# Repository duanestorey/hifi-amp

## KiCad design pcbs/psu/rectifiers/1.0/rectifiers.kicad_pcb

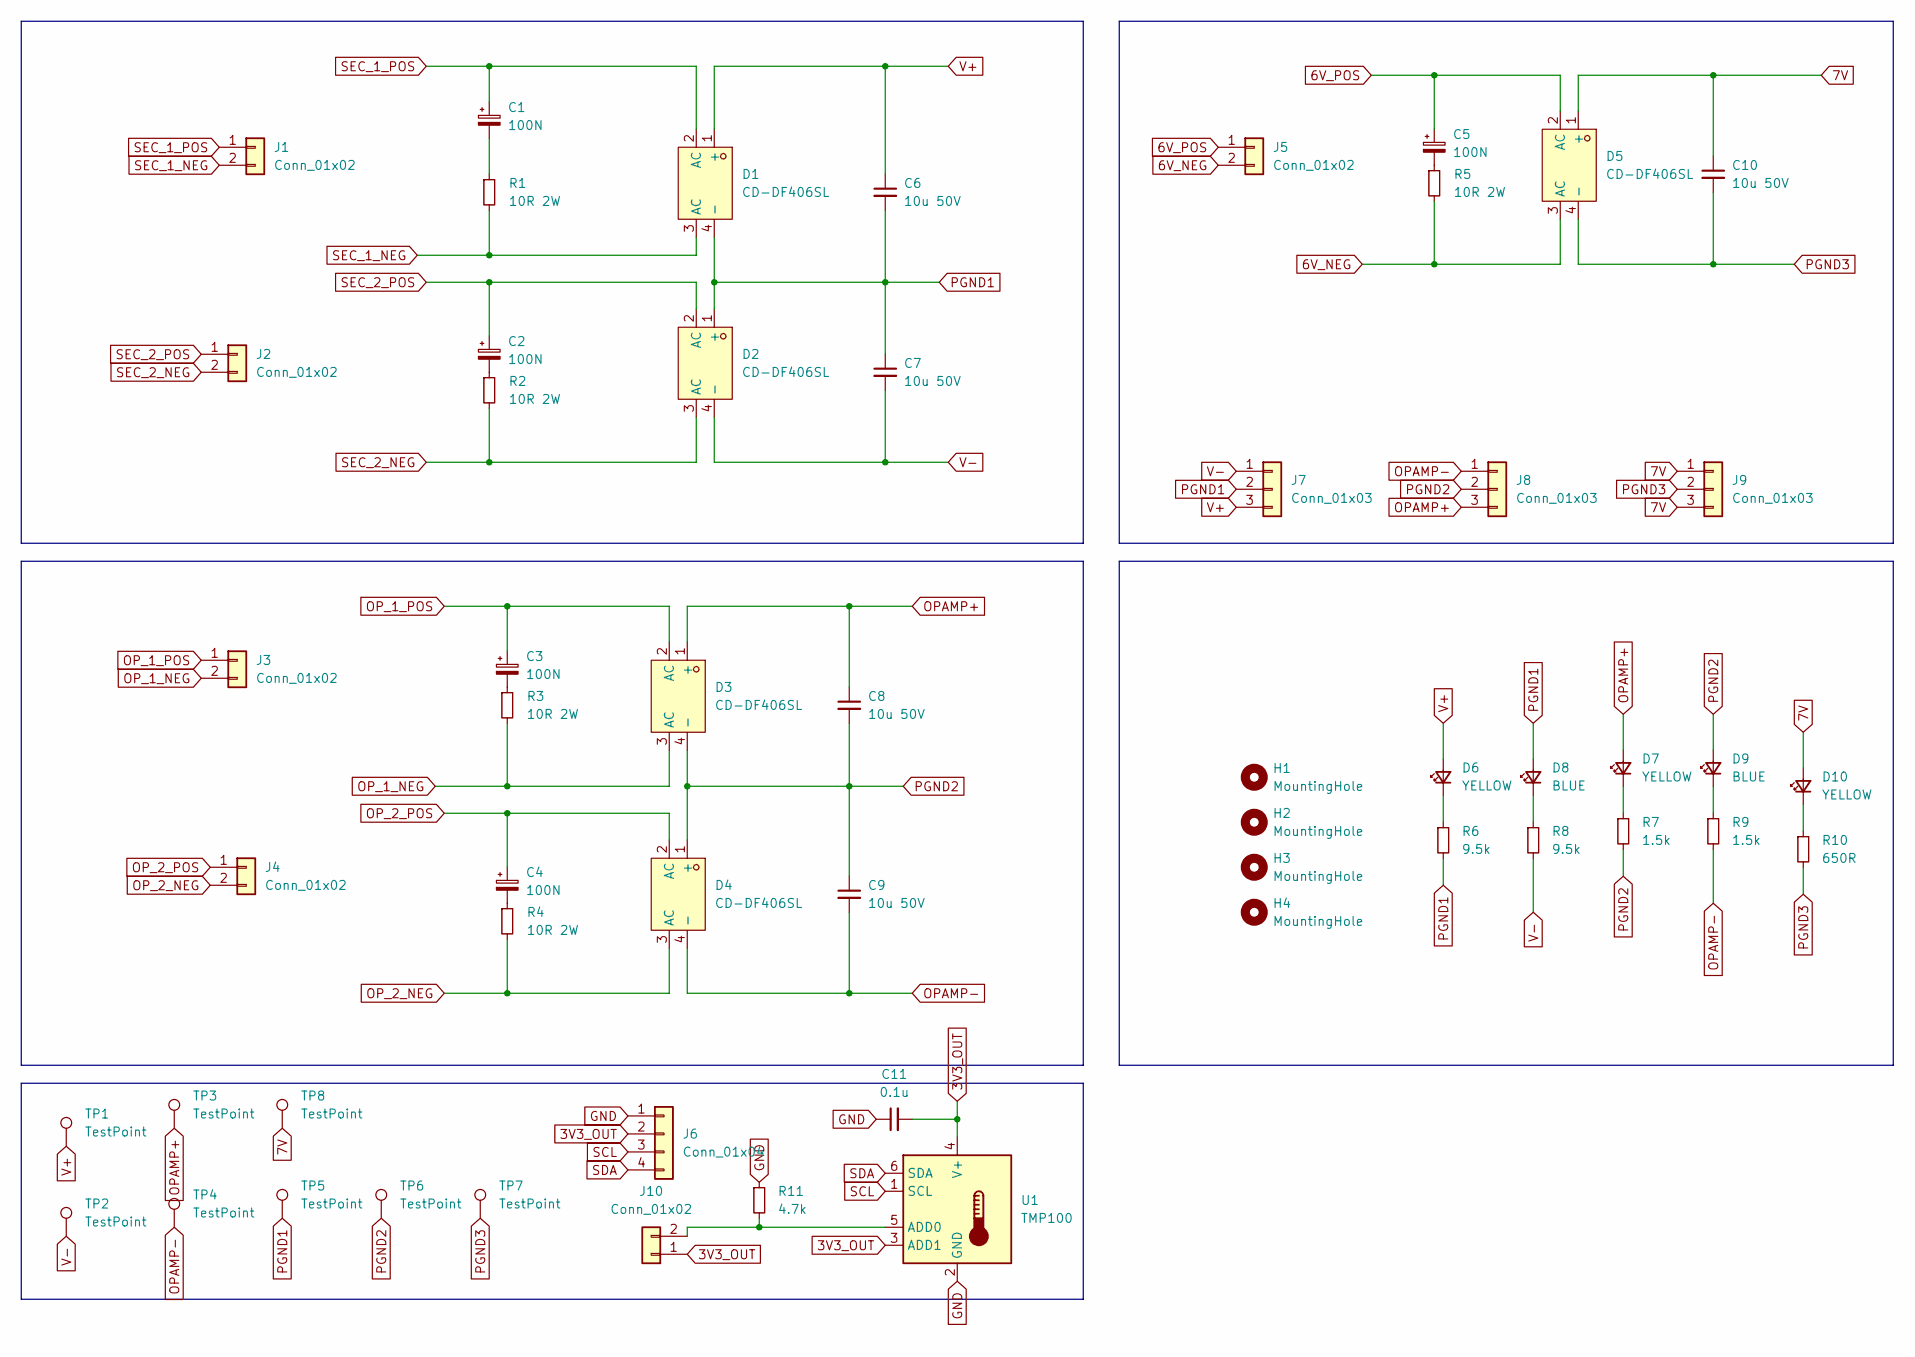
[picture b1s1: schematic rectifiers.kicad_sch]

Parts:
C1, C2, C3, C4, C5: 100N; C_Rect_L10.3mm_W4.5mm_P7.50mm_MKS4; Mouser MKP4F031002D00KF00
C6, C7, C8, C9, C10: 10u 50V; C_1206_3216Metric_Pad1.33x1.80mm_HandSolder
C11: 0.1u; C_0805_2012Metric_Pad1.18x1.45mm_HandSolder
D1, D2, D3, D4, D5: CD-DF406SL; Z4-D_4P-L10.5-W8.1-P5.08-TL; LCSC Part C17188088
D6, D7, D10: YELLOW; LED_0805_2012Metric_Pad1.15x1.40mm_HandSolder
D8, D9: BLUE; LED_0805_2012Metric_Pad1.15x1.40mm_HandSolder
H1, H2, H3, H4: MountingHole; MountingHole_3.2mm_M3_DIN965_Pad_TopBottom
J1, J2, J3, J4, J5: Conn_01x02; TerminalBlock_Phoenix_PT-1,5-2-3.5-H_1x02_P3.50mm_Horizontal
J6: Conn_01x04; JST_PH_B4B-PH-K_1x04_P2.00mm_Vertical
J7, J8, J9: Conn_01x03; JST_VH_B3P-VH-B_1x03_P3.96mm_Vertical
J10: Conn_01x02; PinHeader_1x02_P2.54mm_Vertical
R1, R2, R3, R4, R5: 10R 2W; R_2512_6332Metric_Pad1.40x3.35mm_HandSolder; Mouser 603-SR2512JK-7W10RL
R6, R8: 9.5k; R_0805_2012Metric_Pad1.20x1.40mm_HandSolder
R7, R9: 1.5k; R_0805_2012Metric_Pad1.20x1.40mm_HandSolder
R10: 650R; R_0805_2012Metric_Pad1.20x1.40mm_HandSolder
R11: 4.7k; R_0805_2012Metric_Pad1.20x1.40mm_HandSolder
TP1, TP2, TP3, TP4, TP5, TP6, TP7, TP8: TestPoint; TestPoint_THTPad_2.5x2.5mm_Drill1.2mm
U1: TMP100; SOT-23-6

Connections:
3V3_OUT: C11.2, J6.2, J10.1, U1.3 (ADD1), U1.4 (V+)
6V_NEG: D5.3 (AC), J5.2, R5.2
6V_POS: C5.1, D5.2 (AC), J5.1
7V: C10.1, D5.1 (+), D10.2 (A), J9.1, J9.3, TP8.1
GND: C11.1, J6.1, R11.1, U1.2 (GND)
unnamed: C1.2, R1.1
unnamed: C2.2, R2.1
unnamed: C3.2, R3.1
unnamed: C4.2, R4.1
unnamed: C5.2, R5.1
unnamed: D6.1 (K), R6.1
unnamed: D7.1 (K), R7.1
unnamed: D8.1 (K), R8.1
unnamed: D9.1 (K), R9.1
unnamed: D10.1 (K), R10.1
unnamed: J10.2, R11.2, U1.5 (ADD0)
OPAMP+: C8.1, D3.1 (+), D7.2 (A), J8.3, TP3.1
OPAMP-: C9.2, D4.4 (-), J8.1, R9.2, TP4.1
OP_1_NEG: D3.3 (AC), J3.2, R3.2
OP_1_POS: C3.1, D3.2 (AC), J3.1
OP_2_NEG: D4.3 (AC), J4.2, R4.2
OP_2_POS: C4.1, D4.2 (AC), J4.1
PGND1: C6.2, C7.1, D1.4 (-), D2.1 (+), D8.2 (A), J7.2, R6.2, TP5.1
PGND2: C8.2, C9.1, D3.4 (-), D4.1 (+), D9.2 (A), J8.2, R7.2, TP6.1
PGND3: C10.2, D5.4 (-), J9.2, R10.2, TP7.1
SCL: J6.3, U1.1 (SCL)
SDA: J6.4, U1.6 (SDA)
SEC_1_NEG: D1.3 (AC), J1.2, R1.2
SEC_1_POS: C1.1, D1.2 (AC), J1.1
SEC_2_NEG: D2.3 (AC), J2.2, R2.2
SEC_2_POS: C2.1, D2.2 (AC), J2.1
V+: C6.1, D1.1 (+), D6.2 (A), J7.3, TP1.1
V-: C7.2, D2.4 (-), J7.1, R8.2, TP2.1

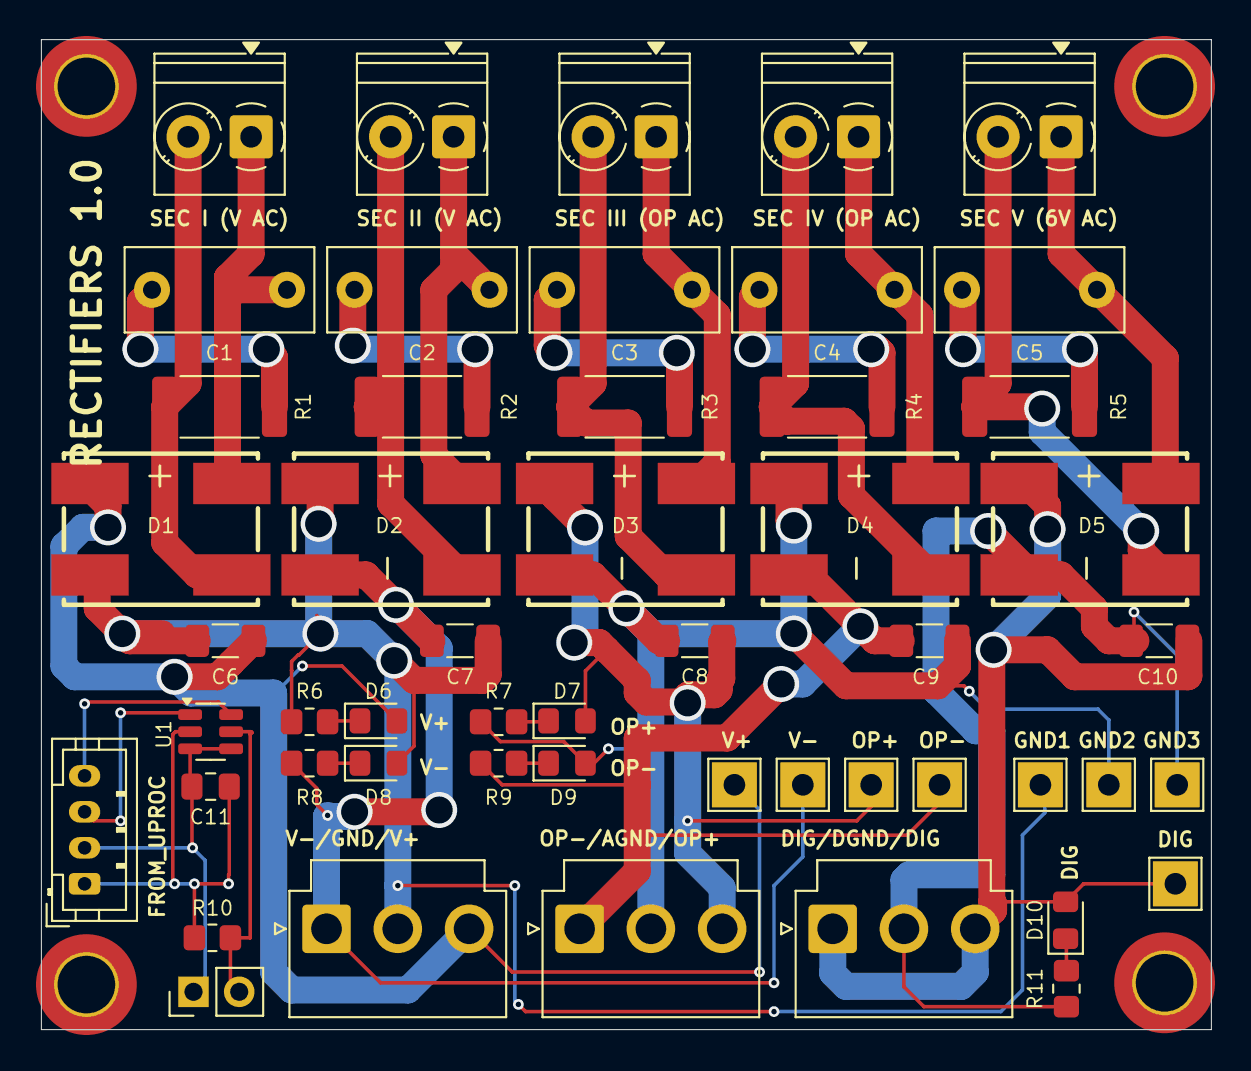
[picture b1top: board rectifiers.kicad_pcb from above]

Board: 2 copper layers, 65.0 x 55.0 mm, 55 parts (0 on the bottom side), 33 nets.

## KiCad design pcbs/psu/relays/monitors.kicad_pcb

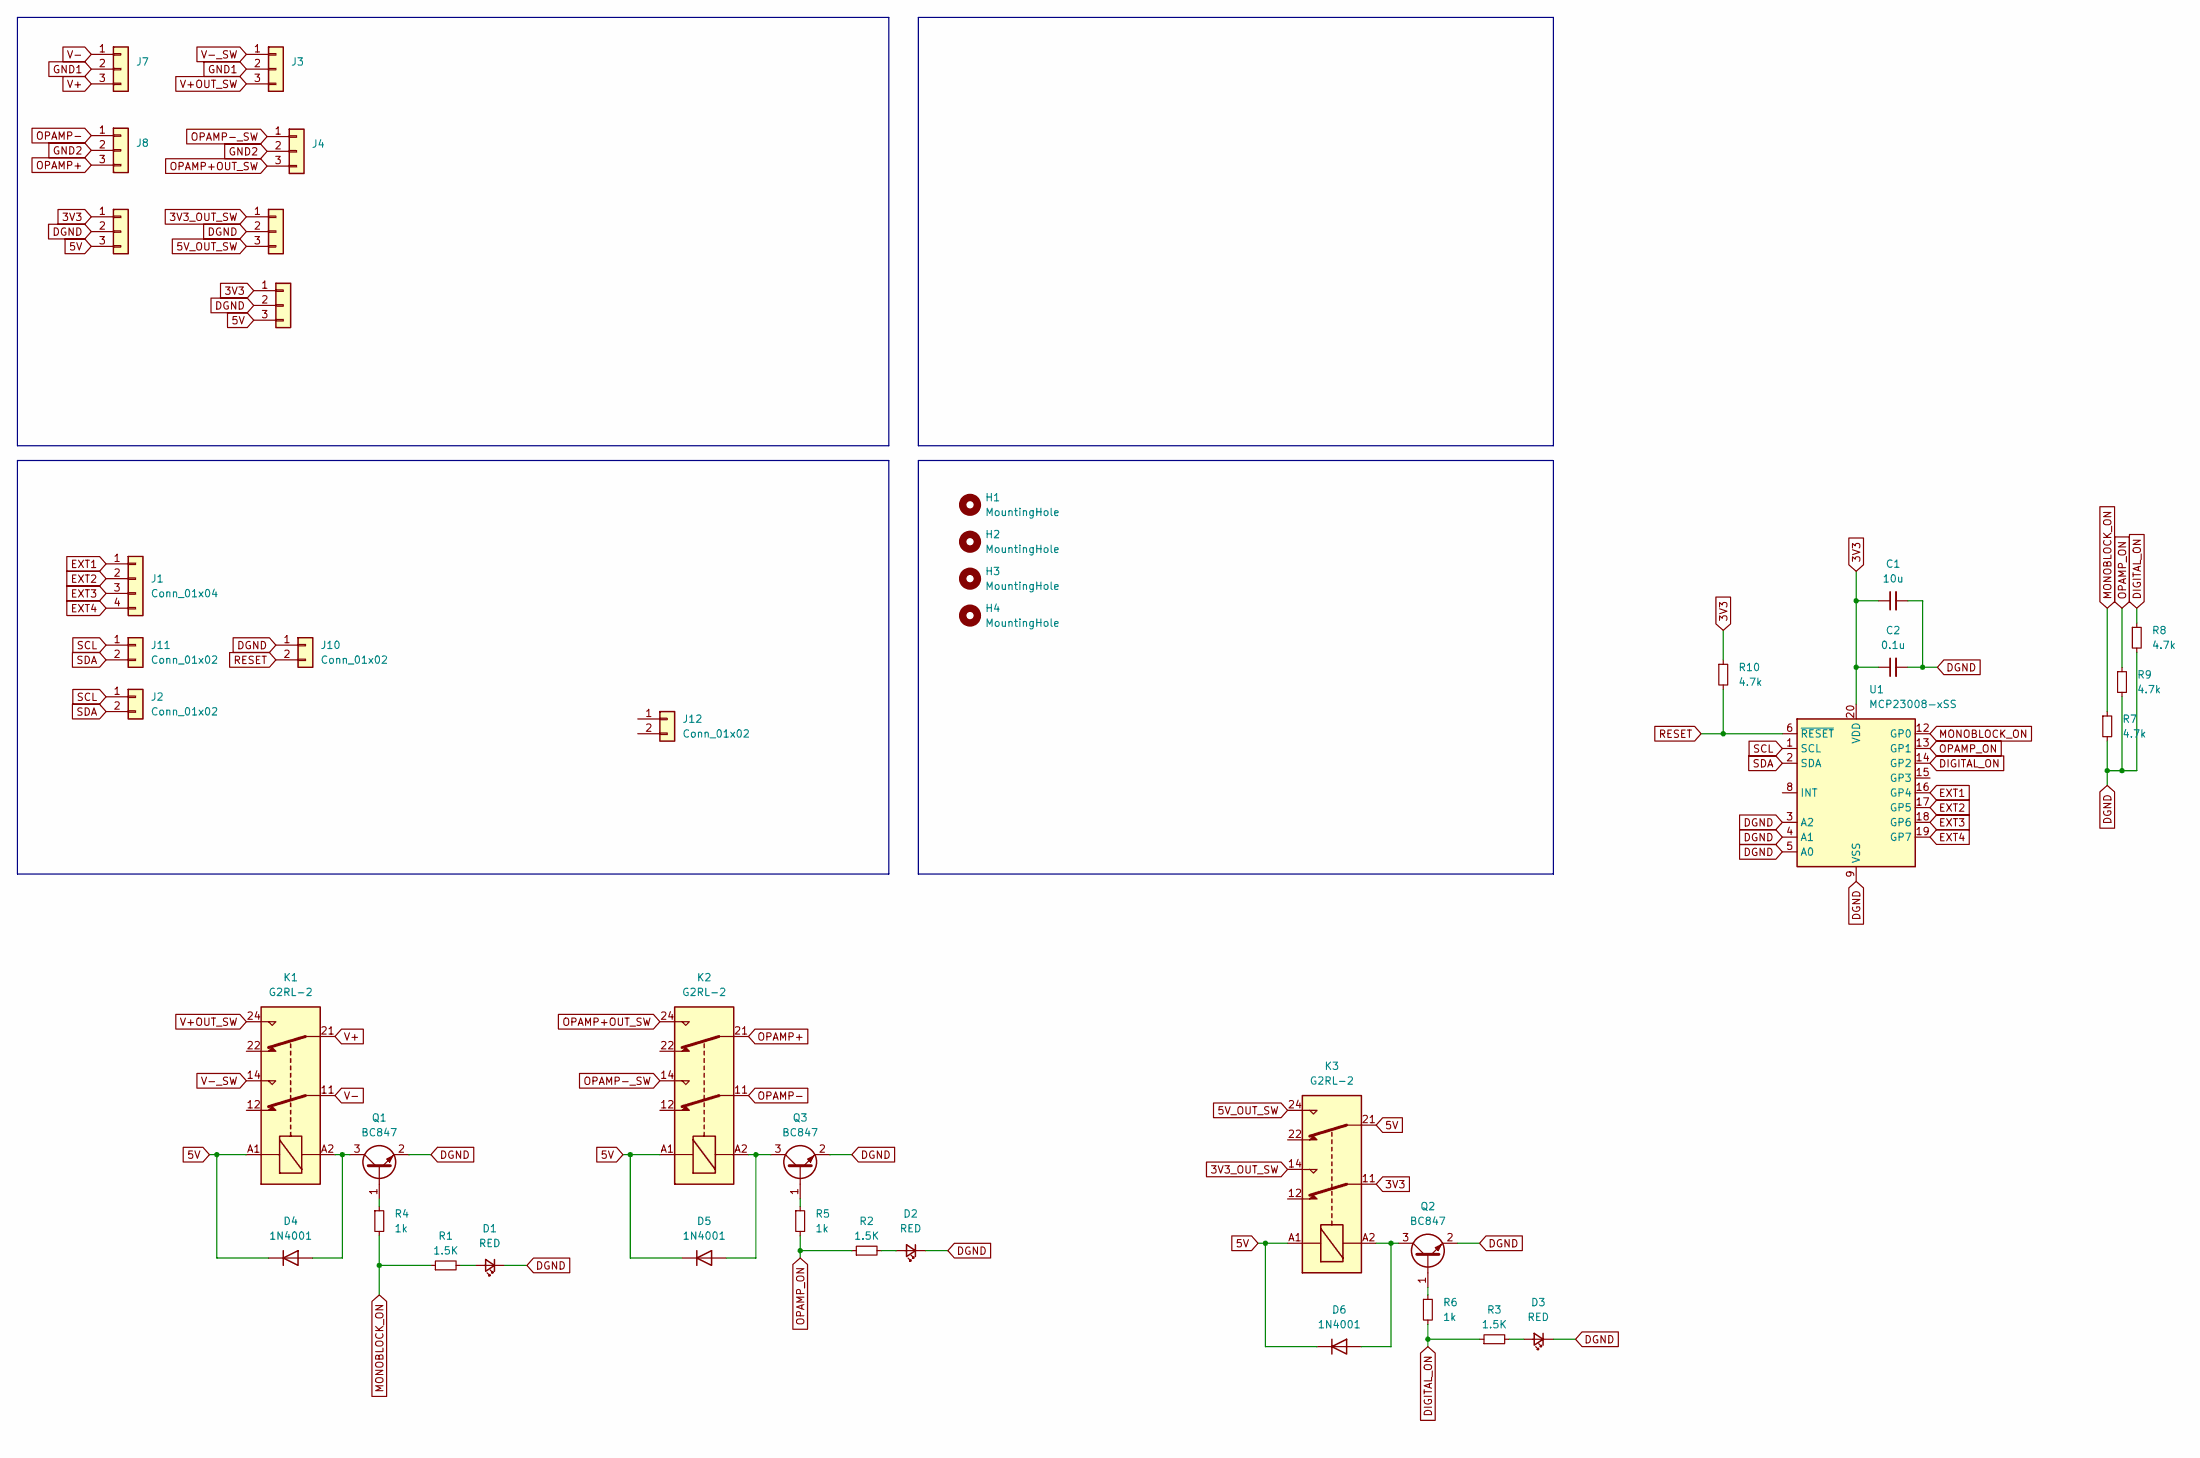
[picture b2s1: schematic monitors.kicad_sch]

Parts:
C1: 10u; C_1206_3216Metric_Pad1.33x1.80mm_HandSolder
C2: 0.1u; C_0805_2012Metric_Pad1.18x1.45mm_HandSolder
D1, D2, D3: RED; LED_0805_2012Metric_Pad1.15x1.40mm_HandSolder
D4, D5, D6: 1N4001; D_SMA
H1, H2, H3, H4: MountingHole; MountingHole_3.2mm_M3_DIN965_Pad_TopBottom
J1: Conn_01x04; JST_PH_B4B-PH-K_1x04_P2.00mm_Vertical
J2, J10, J11: Conn_01x02; JST_PH_B2B-PH-K_1x02_P2.00mm_Vertical
J3, J4, J5, J6, J7, J8, J9: Conn_01x03; JST_VH_B3P-VH-B_1x03_P3.96mm_Vertical
J12: Conn_01x02
K1, K2, K3: G2RL-2; Relay_DPDT_Omron_G2RL-2
Q1, Q2, Q3: BC847; SOT-23
R1, R2, R3: 1.5K; R_0805_2012Metric_Pad1.20x1.40mm_HandSolder
R4, R5, R6: 1k; R_0805_2012Metric_Pad1.20x1.40mm_HandSolder
R7, R8, R9, R10: 4.7k; R_0805_2012Metric_Pad1.20x1.40mm_HandSolder
U1: MCP23008-xSS; SSOP-20_5.3x7.2mm_P0.65mm

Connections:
3V3: C1.1, C2.1, J5.1, J9.1, K3.11, R10.1, U1.20 (VDD)
3V3_OUT_SW: J6.1, K3.14
5V: D4.1 (K), D5.1 (K), D6.1 (K), J5.3, J9.3, K1.A1, K2.A1, K3.21, K3.A1
5V_OUT_SW: J6.3, K3.24
DGND: C1.2, C2.2, D1.1 (K), D2.1 (K), D3.1 (K), J5.2, J6.2, J9.2, J10.1, Q1.2 (E), Q2.2 (E), Q3.2 (E), R7.2, R8.2, R9.2, U1.3 (A2), U1.4 (A1), U1.5 (A0), U1.9 (VSS)
DIGITAL_ON: R3.1, R6.2, R8.1, U1.14 (GP2)
EXT1: J1.1, U1.16 (GP4)
EXT2: J1.2, U1.17 (GP5)
EXT3: J1.3, U1.18 (GP6)
EXT4: J1.4, U1.19 (GP7)
GND1: J3.2, J7.2
GND2: J4.2, J8.2
MONOBLOCK_ON: R1.1, R4.2, R7.1, U1.12 (GP0)
unnamed: D1.2 (A), R1.2
unnamed: D2.2 (A), R2.2
unnamed: D3.2 (A), R3.2
unnamed: D4.2 (A), K1.A2, Q1.3 (C)
unnamed: D5.2 (A), K2.A2, Q3.3 (C)
unnamed: D6.2 (A), K3.A2, Q2.3 (C)
unnamed: Q1.1 (B), R4.1
unnamed: Q2.1 (B), R6.1
unnamed: Q3.1 (B), R5.1
OPAMP+: J8.3, K2.21
OPAMP+OUT_SW: J4.3, K2.24
OPAMP-: J8.1, K2.11
OPAMP-_SW: J4.1, K2.14
OPAMP_ON: R2.1, R5.2, R9.1, U1.13 (GP1)
RESET: J10.2, R10.2, U1.6 (~RESET)
SCL: J2.1, J11.1, U1.1 (SCL)
SDA: J2.2, J11.2, U1.2 (SDA)
V+: J7.3, K1.21
V+OUT_SW: J3.3, K1.24
V-: J7.1, K1.11
V-_SW: J3.1, K1.14

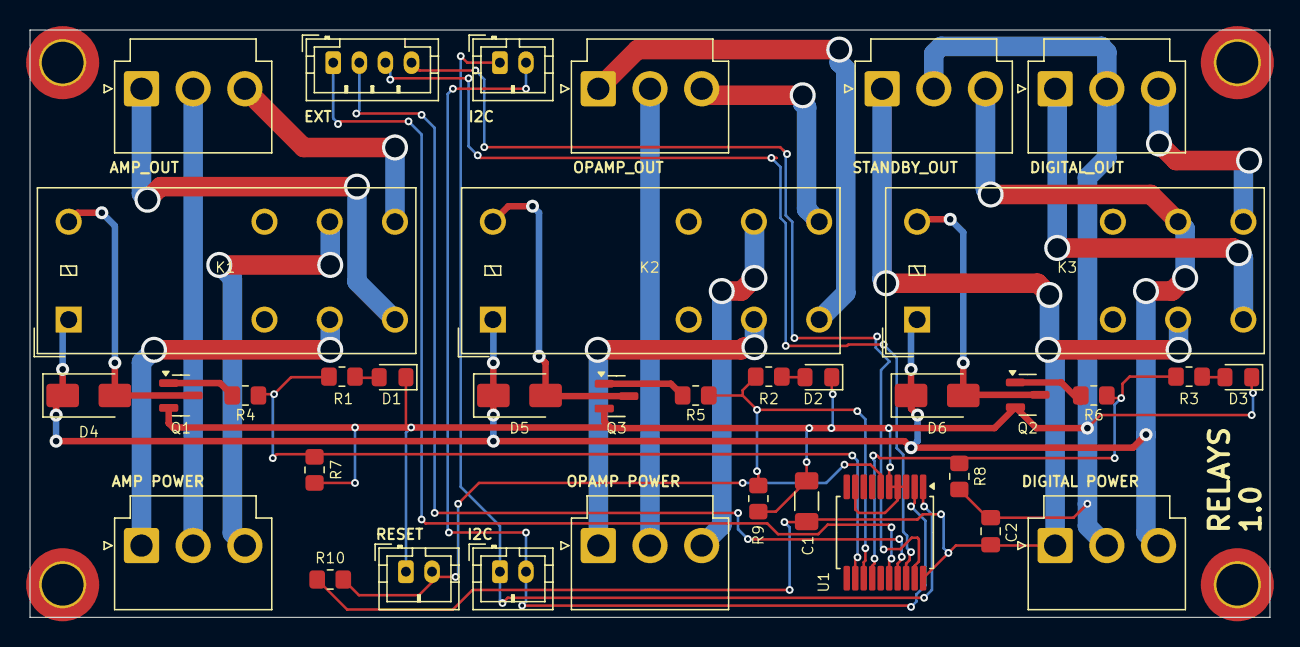
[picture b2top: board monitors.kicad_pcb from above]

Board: 2 copper layers, 95.0 x 45.0 mm, 40 parts (0 on the bottom side), 34 nets.

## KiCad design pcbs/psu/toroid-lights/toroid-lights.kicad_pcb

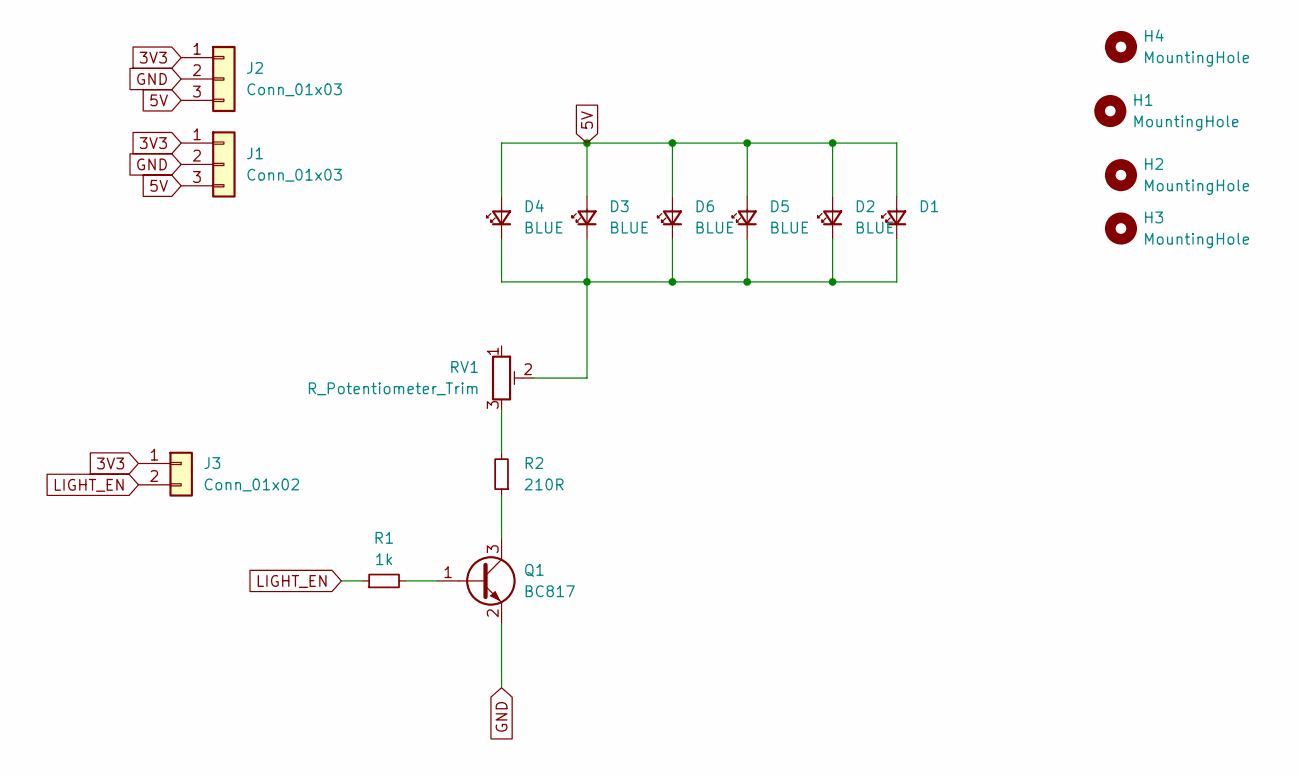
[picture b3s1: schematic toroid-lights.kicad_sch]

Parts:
D1, D2, D3, D4, D5, D6: BLUE; LED_0805_2012Metric_Pad1.15x1.40mm_HandSolder
H1, H2, H3, H4: MountingHole; MountingHole_3.2mm_M3_DIN965_Pad_TopBottom
J1, J2: Conn_01x03; JST_VH_B3P-VH-B_1x03_P3.96mm_Vertical
J3: Conn_01x02; PinHeader_1x02_P2.54mm_Vertical
Q1: BC817; SOT-23
R1: 1k; R_0805_2012Metric_Pad1.20x1.40mm_HandSolder
R2: 210R; R_0805_2012Metric_Pad1.20x1.40mm_HandSolder
RV1: R_Potentiometer_Trim; Potentiometer_Bourns_3296W_Vertical

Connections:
3V3: J1.1, J2.1, J3.1
5V: D1.2 (A), D2.2 (A), D3.2 (A), D4.2 (A), D5.2 (A), D6.2 (A), J1.3, J2.3
GND: J1.2, J2.2, Q1.2 (E)
LIGHT_EN: J3.2, R1.1
unnamed: D1.1 (K), D2.1 (K), D3.1 (K), D4.1 (K), D5.1 (K), D6.1 (K), RV1.2
unnamed: Q1.1 (B), R1.2
unnamed: Q1.3 (C), R2.1
unnamed: R2.2, RV1.3

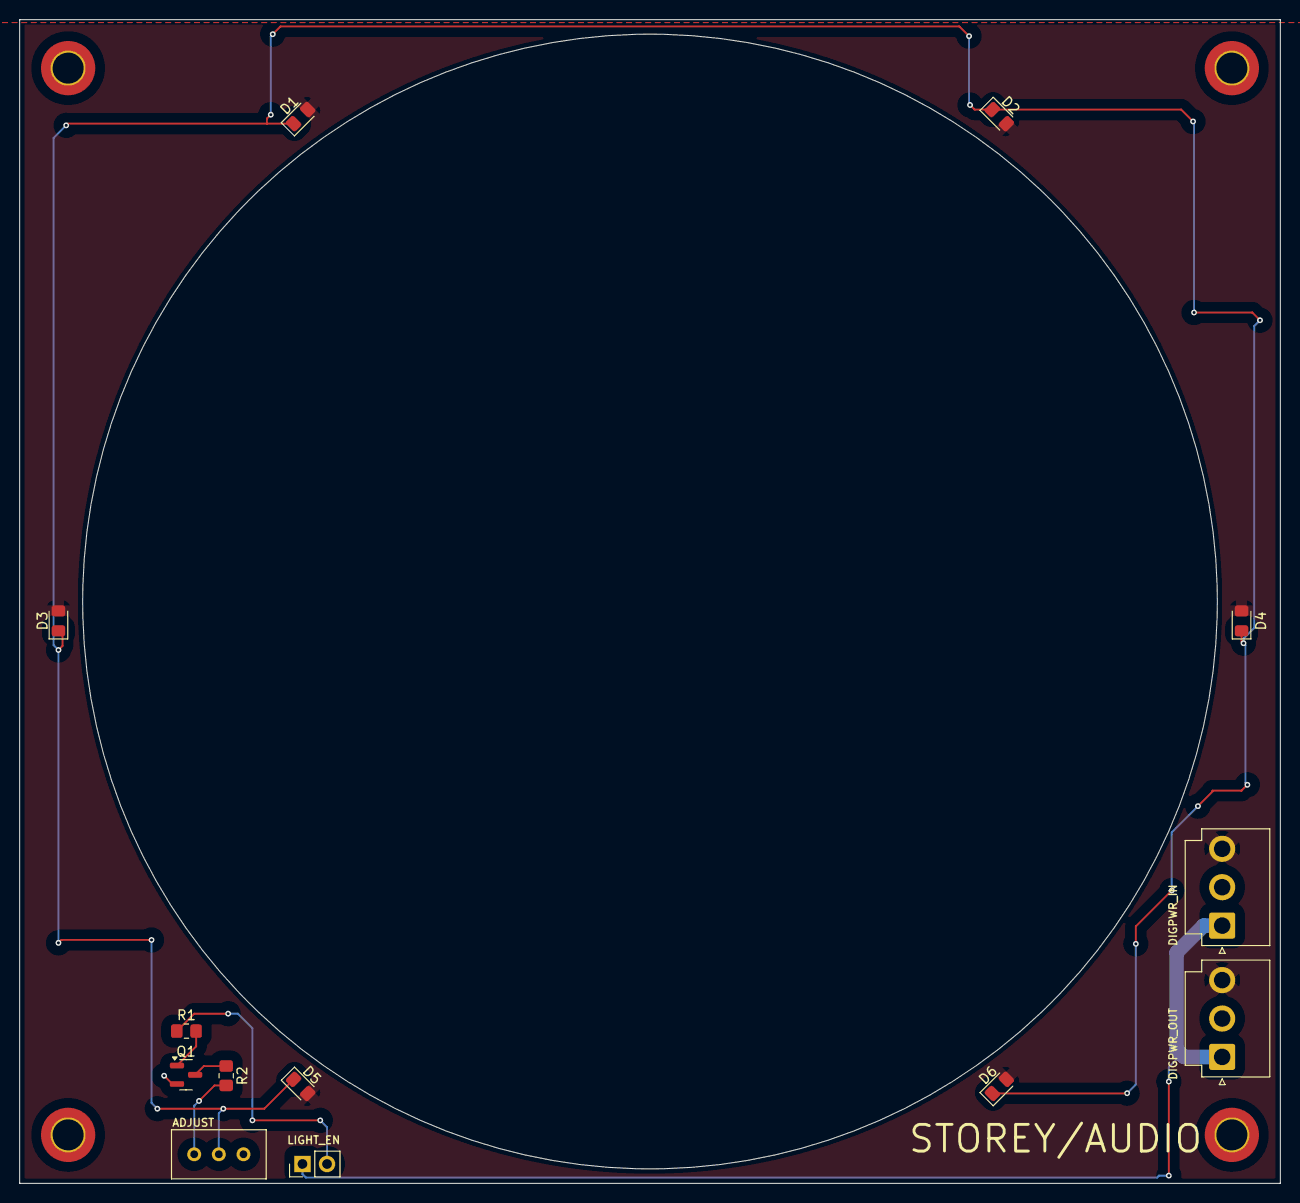
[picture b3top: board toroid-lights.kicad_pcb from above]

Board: 2 copper layers, 130.0 x 120.0 mm, 17 parts (0 on the bottom side), 8 nets.

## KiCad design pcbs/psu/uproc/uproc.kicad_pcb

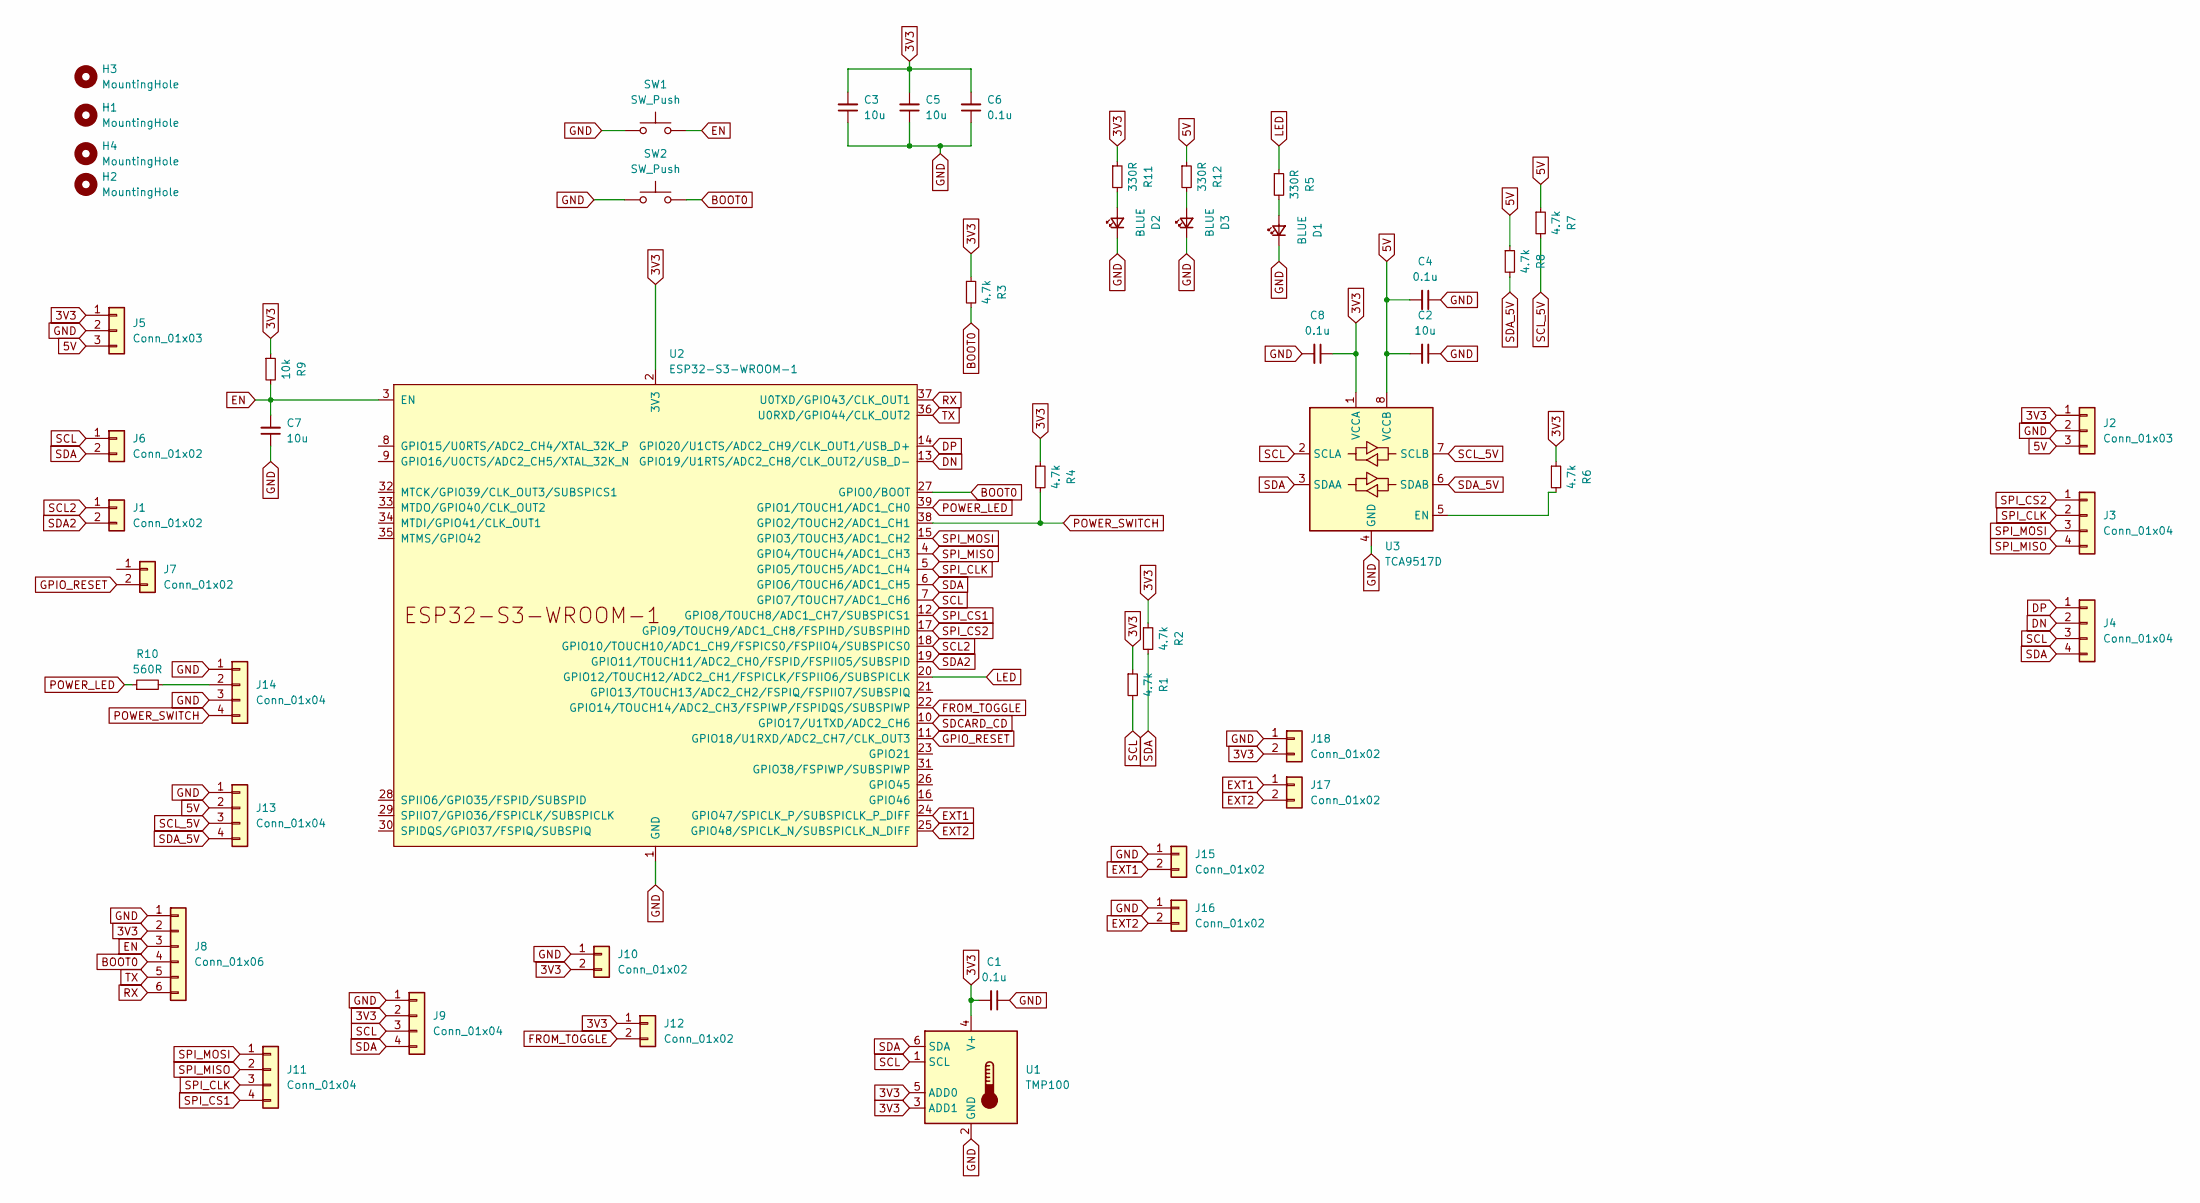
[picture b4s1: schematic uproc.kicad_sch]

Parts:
C1, C4, C6, C8: 0.1u; C_0805_2012Metric_Pad1.18x1.45mm_HandSolder
C2, C3, C5, C7: 10u; C_1206_3216Metric_Pad1.33x1.80mm_HandSolder
D1, D2, D3: BLUE; LED_0805_2012Metric_Pad1.15x1.40mm_HandSolder
H1, H2, H3, H4: MountingHole; MountingHole_3.2mm_M3_DIN965_Pad_TopBottom
J1, J6, J7, J10, J12, J15, J16: Conn_01x02; JST_PH_B2B-PH-K_1x02_P2.00mm_Vertical
J2, J5: Conn_01x03; JST_PH_B3B-PH-K_1x03_P2.00mm_Vertical
J3, J4, J9, J11, J13, J14: Conn_01x04; JST_PH_B4B-PH-K_1x04_P2.00mm_Vertical
J8: Conn_01x06; PinHeader_1x06_P2.54mm_Vertical
J17, J18: Conn_01x02; PinHeader_1x02_P2.54mm_Vertical
R1, R2, R3, R4, R6, R7, R8: 4.7k; R_0805_2012Metric_Pad1.20x1.40mm_HandSolder
R5, R11, R12: 330R; R_0805_2012Metric_Pad1.20x1.40mm_HandSolder
R9: 10k; R_0805_2012Metric_Pad1.20x1.40mm_HandSolder
R10: 560R; R_0805_2012Metric_Pad1.20x1.40mm_HandSolder
SW1, SW2: SW_Push; Button Aliexpress 4x4
U1: TMP100; SOT-23-6
U2: ESP32-S3-WROOM-1
U3: TCA9517D; SOIC-8_3.9x4.9mm_P1.27mm

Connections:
3V3: C1.2, C3.2, C5.2, C6.2, C8.1, J2.1, J5.1, J8.2, J9.2, J10.2, J12.1, J18.2, R1.1, R2.1, R3.1, R4.1, R6.1, R9.1, R11.1, U1.3 (ADD1), U1.4 (V+), U1.5 (ADD0), U2.2 (3V3), U3.1 (VCCA)
5V: C2.2, C4.2, J2.3, J5.3, J13.2, R7.1, R8.1, R12.1, U3.8 (VCCB)
BOOT0: J8.4, R3.2, SW2.2, U2.27 (GPIO0/BOOT)
DN: J4.2, U2.13 (GPIO19/U1RTS/ADC2_CH8/CLK_OUT2/USB_D-)
DP: J4.1, U2.14 (GPIO20/U1CTS/ADC2_CH9/CLK_OUT1/USB_D+)
EN: C7.2, J8.3, R9.2, SW1.2, U2.3 (EN)
EXT1: J15.2, J17.1, U2.24 (GPIO47/SPICLK_P/SUBSPICLK_P_DIFF)
EXT2: J16.2, J17.2, U2.25 (GPIO48/SPICLK_N/SUBSPICLK_N_DIFF)
FROM_TOGGLE: J12.2, U2.22 (GPIO14/TOUCH14/ADC2_CH3/FSPIWP/FSPIDQS/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)
GND: C1.1, C2.1, C3.1, C4.1, C5.1, C6.1, C7.1, C8.2, D1.1 (K), D2.1 (K), D3.1 (K), J2.2, J5.2, J8.1, J9.1, J10.1, J13.1, J14.1, J14.3, J15.1, J16.1, J18.1, SW1.1, SW2.1, U1.2 (GND), U2.1 (GND), U2.40 (GND), U2.41 (GND), U3.4 (GND)
GPIO_RESET: J7.2, U2.11 (GPIO18/U1RXD/ADC2_CH7/CLK_OUT3)
LED: R5.1, U2.20 (GPIO12/TOUCH12/ADC2_CH1/FSPICLK/FSPIIO6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)
unnamed: D1.2 (A), R5.2
unnamed: D2.2 (A), R11.2
unnamed: D3.2 (A), R12.2
unnamed: J14.2, R10.2
unnamed: R6.2, U3.5 (EN)
POWER_LED: R10.1, U2.39 (GPIO1/TOUCH1/ADC1_CH0)
POWER_SWITCH: J14.4, R4.2, U2.38 (GPIO2/TOUCH2/ADC1_CH1)
RX: J8.6, U2.37 (U0TXD/GPIO43/CLK_OUT1)
SCL: J4.3, J6.1, J9.3, R1.2, U1.1 (SCL), U2.7 (GPIO7/TOUCH7/ADC1_CH6), U3.2 (SCLA)
SCL2: J1.1, U2.18 (GPIO10/TOUCH10/ADC1_CH9/FSPICS0/FSPIIO4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)
SCL_5V: J13.3, R7.2, U3.7 (SCLB)
SDA: J4.4, J6.2, J9.4, R2.2, U1.6 (SDA), U2.6 (GPIO6/TOUCH6/ADC1_CH5), U3.3 (SDAA)
SDA2: J1.2, U2.19 (GPIO11/TOUCH11/ADC2_CH0/FSPID/FSPIIO5/S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)
SDA_5V: J13.4, R8.2, U3.6 (SDAB)
SDCARD_CD: U2.10 (GPIO17/U1TXD/ADC2_CH6)
SPI_CLK: J3.2, J11.3, U2.5 (GPIO5/TOUCH5/ADC1_CH4)
SPI_CS1: J11.4, U2.12 (GPIO8/TOUCH8/ADC1_CH7/SUBSPICS1)
SPI_CS2: J3.1, U2.17 (GPIO9/TOUCH9/ADC1_CH8/FSPIHD/SUBSPIHD)
SPI_MISO: J3.4, J11.2, U2.4 (GPIO4/TOUCH4/ADC1_CH3)
SPI_MOSI: J3.3, J11.1, U2.15 (GPIO3/TOUCH3/ADC1_CH2)
TX: J8.5, U2.36 (U0RXD/GPIO44/CLK_OUT2)

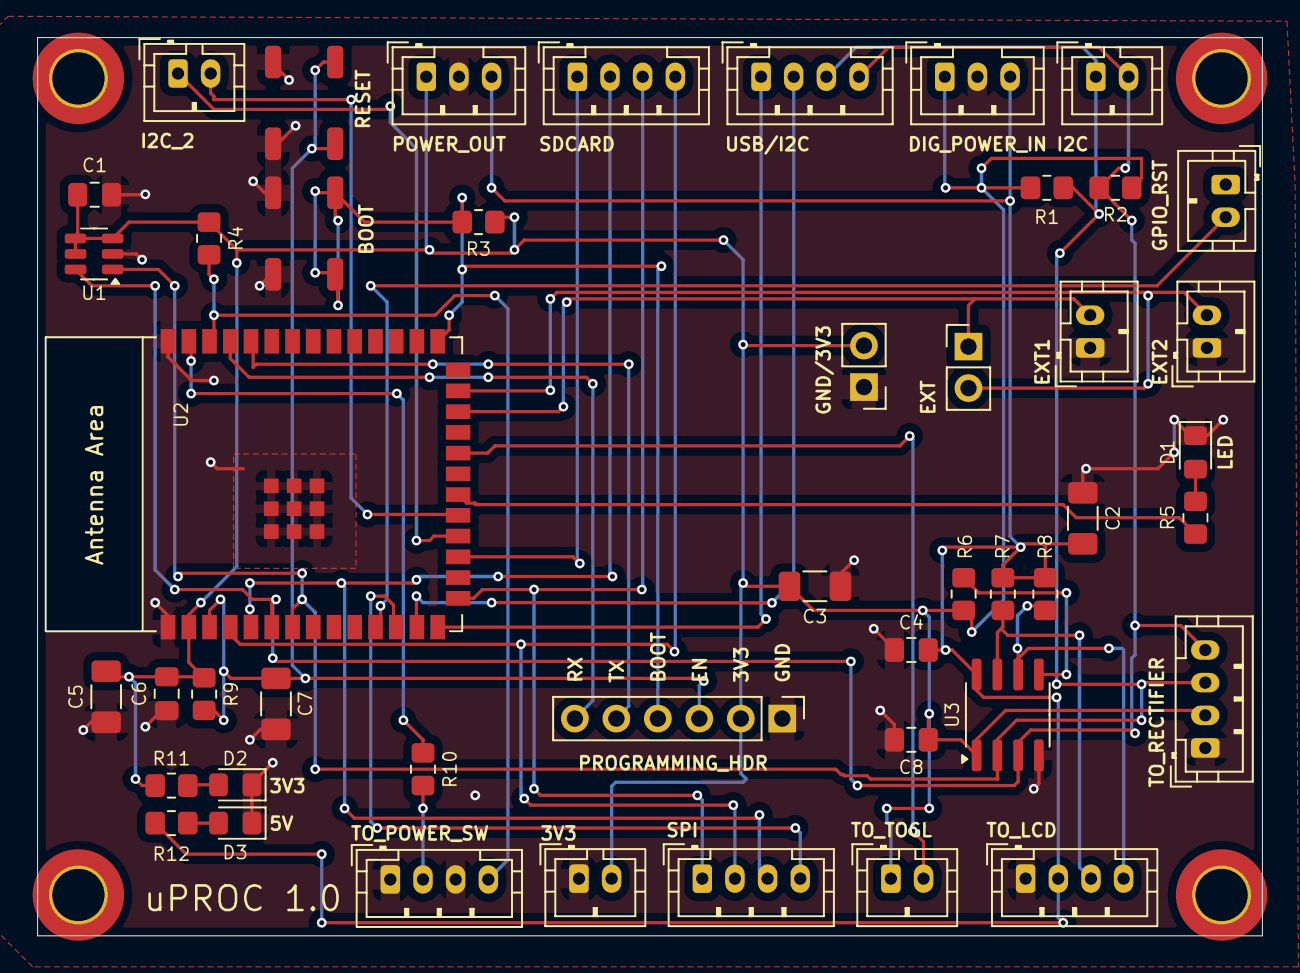
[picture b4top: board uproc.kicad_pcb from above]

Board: 2 copper layers, 75.0 x 55.0 mm, 50 parts (0 on the bottom side), 32 nets.
